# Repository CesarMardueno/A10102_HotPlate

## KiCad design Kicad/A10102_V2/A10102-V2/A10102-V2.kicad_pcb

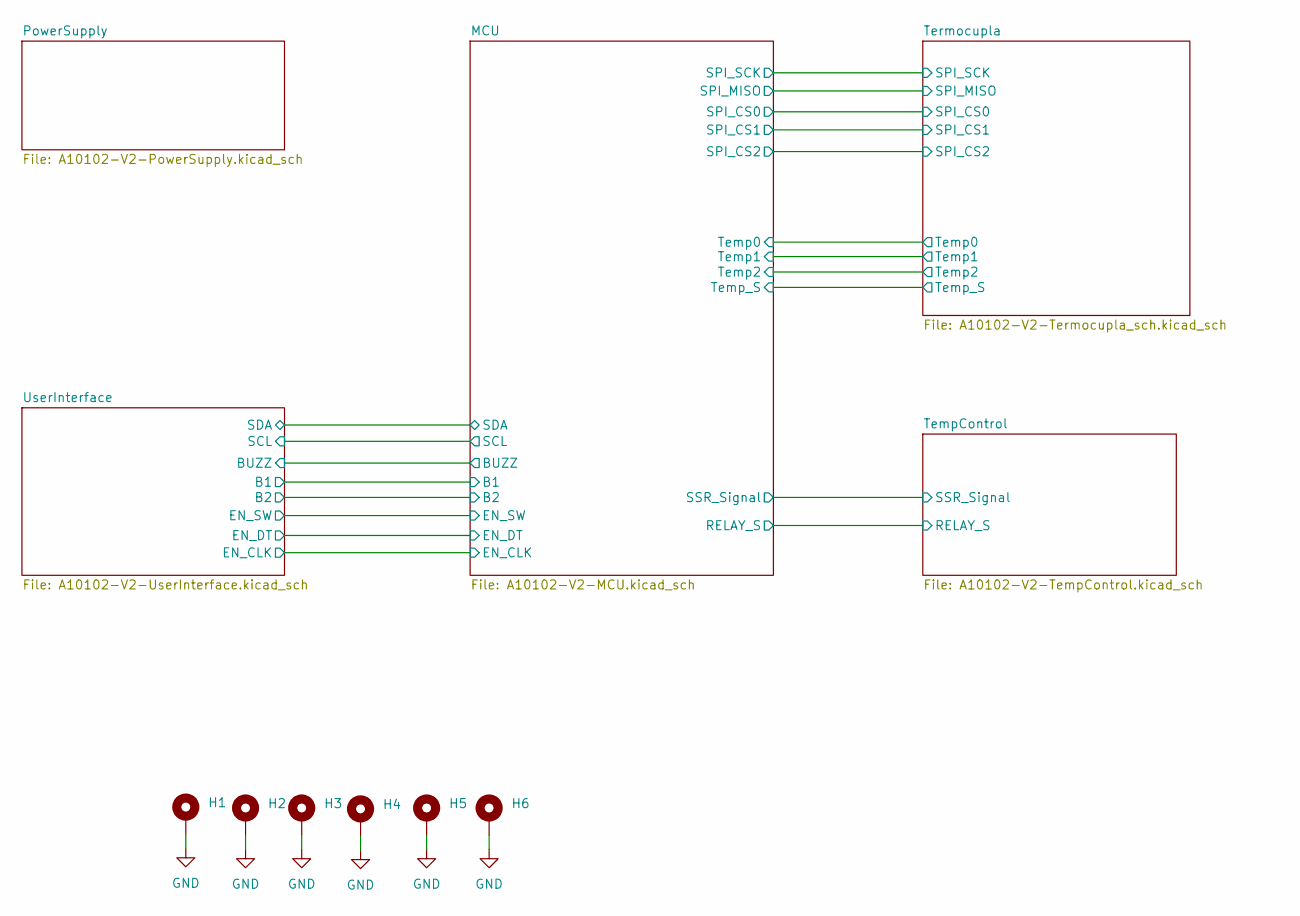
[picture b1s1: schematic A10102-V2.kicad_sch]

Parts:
H1, H2, H3, H4, H5, H6: MountingHole_Pad; MountingHole_3.2mm_M3_ISO7380_Pad

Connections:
GND: H1.1, H2.1, H3.1, H4.1, H5.1, H6.1; also elsewhere on the board

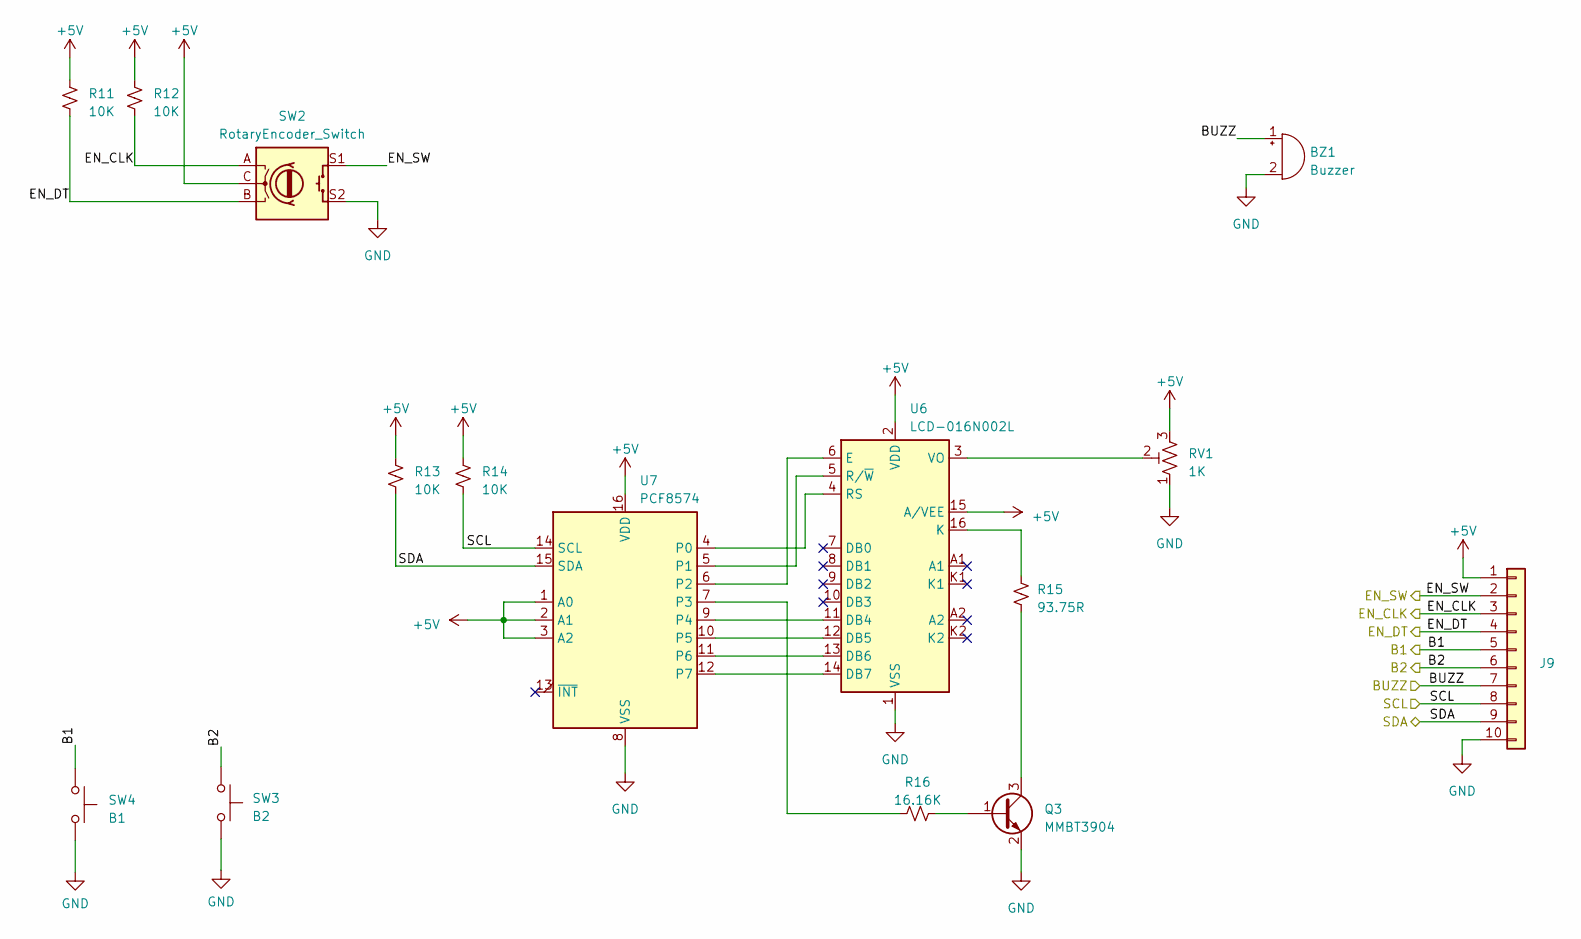
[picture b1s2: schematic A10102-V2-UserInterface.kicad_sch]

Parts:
BZ1: Buzzer; MagneticBuzzer_ProSignal_ABT-410-RC
J9: Conn_01x10; PinHeader_1x10_P2.54mm_Vertical
Q3: MMBT3904; SOT-23
R11, R12, R13, R14: 10K; R_0603_1608Metric_Pad0.98x0.95mm_HandSolder
R15: 93.75R; R_0603_1608Metric_Pad0.98x0.95mm_HandSolder
R16: 16.16K; R_0603_1608Metric_Pad0.98x0.95mm_HandSolder
RV1: 1K; TRIM_3296-W
SW2: RotaryEncoder_Switch; RotaryEncoder_Alps_EC11E-Switch_Vertical_H20mm
SW3: B2; 1TS009C-2400-5000-CT
SW4: B1; 1TS009C-2400-5000-CT
U6: LCD-016N002L
U7: PCF8574; SOIC-16W_7.5x10.3mm_P1.27mm

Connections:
+5V: J9.1, R11.2, R12.2, R13.2, R14.2, RV1.3, SW2.C, U6.2 (VDD), U6.15 (A/VEE), U7.1 (A0), U7.2 (A1), U7.3 (A2), U7.16 (VDD); also elsewhere on the board
/MCU/B1: J9.5, SW4.1; also elsewhere on the board
/MCU/B2: J9.6, SW3.1; also elsewhere on the board
/MCU/BUZZ: BZ1.1 (-), J9.7; also elsewhere on the board
/MCU/EN_CLK: J9.3, R12.1, SW2.A; also elsewhere on the board
/MCU/EN_DT: J9.4, R11.1, SW2.B; also elsewhere on the board
/MCU/EN_SW: J9.2, SW2.S1; also elsewhere on the board
/MCU/SCL: J9.8, R14.1, U7.14 (SCL); also elsewhere on the board
/MCU/SDA: J9.9, R13.1, U7.15 (SDA); also elsewhere on the board
GND: BZ1.2 (+), J9.10, Q3.2 (E), RV1.1, SW2.S2, SW3.2, SW4.2, U6.1 (VSS), U7.8 (VSS); also elsewhere on the board
unnamed: Q3.1 (B), R16.2
unnamed: Q3.3 (C), R15.1
unnamed: U6.11 (DB4), U7.9 (P4)
unnamed: U6.12 (DB5), U7.10 (P5)
unnamed: U6.13 (DB6), U7.11 (P6)
unnamed: U6.14 (DB7), U7.12 (P7)
unnamed: U6.6 (E), U7.6 (P2)
unnamed: R15.2, U6.16 (K)
unnamed: U6.4 (RS), U7.4 (P0)
unnamed: U6.5 (R/~W), U7.5 (P1)
unnamed: RV1.2, U6.3 (VO)
unnamed: R16.1, U7.7 (P3)

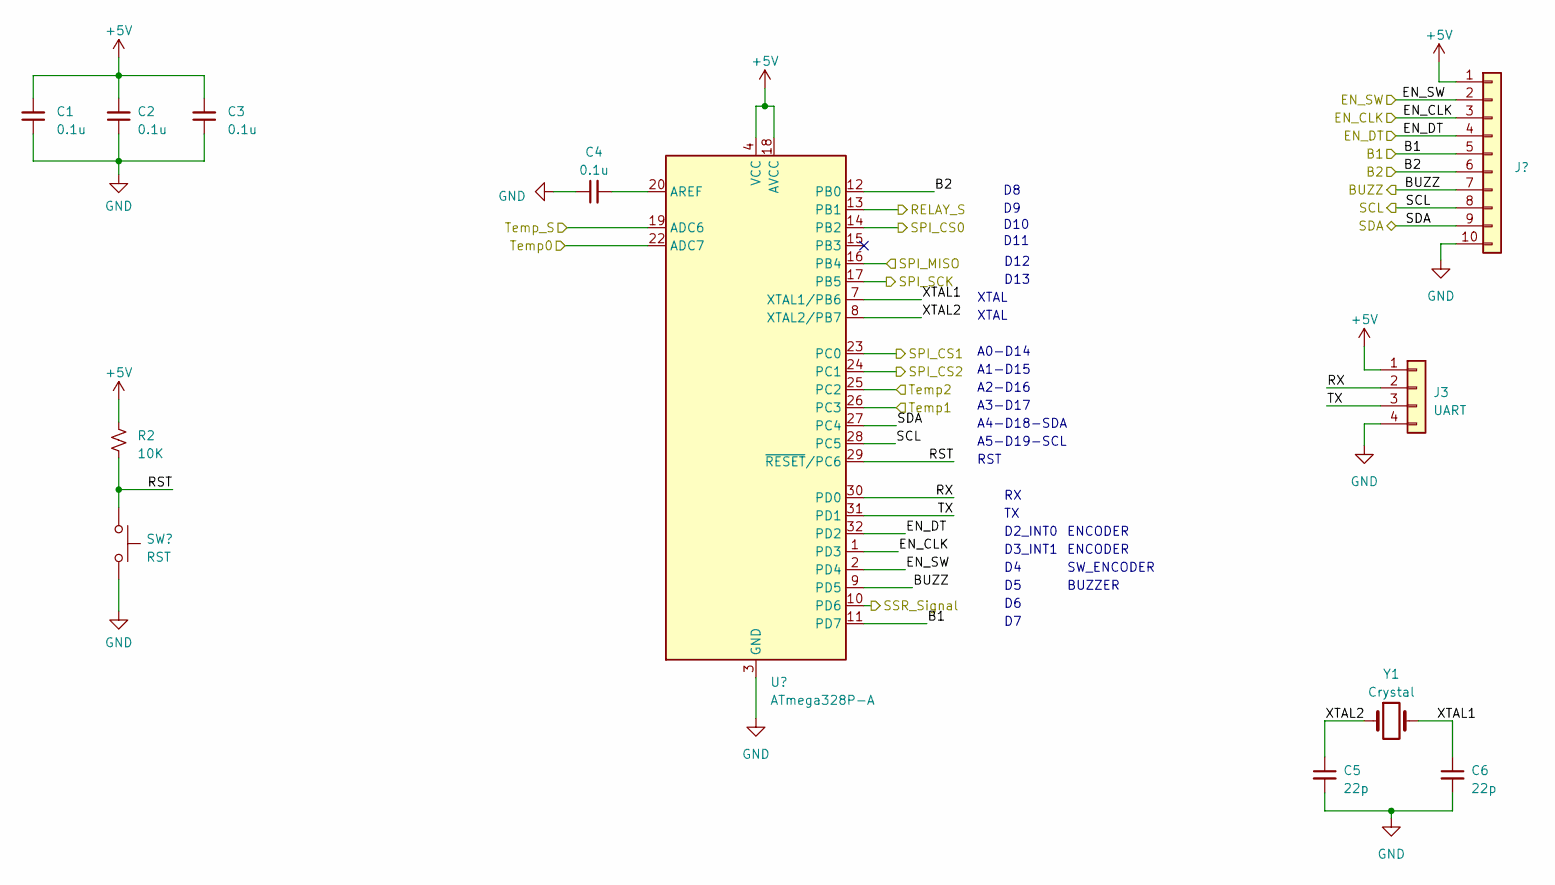
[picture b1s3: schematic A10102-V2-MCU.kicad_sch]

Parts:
C1, C2, C3, C4: 0.1u; C_0603_1608Metric_Pad1.08x0.95mm_HandSolder
C5, C6: 22p; C_0603_1608Metric_Pad1.08x0.95mm_HandSolder
J2: Conn_01x10; PinHeader_1x10_P2.54mm_Vertical
J3: UART; PinHeader_1x04_P2.54mm_Vertical
R2: 10K; R_0603_1608Metric_Pad0.98x0.95mm_HandSolder
SW1: RST; SW_PUSH_6mm_H5mm
U1: ATmega328P-A; TQFP-32_7x7mm_P0.8mm
Y1: Crystal; Crystal_HC52-8mm_Vertical

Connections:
+5V: C1.2, C2.2, C3.2, J2.1, J3.1, R2.1, U1.4 (VCC), U1.6 (VCC), U1.18 (AVCC); also elsewhere on the board
/MCU/B1: J2.5, U1.11 (PD7); also elsewhere on the board
/MCU/B2: J2.6, U1.12 (PB0); also elsewhere on the board
/MCU/BUZZ: J2.7, U1.9 (PD5); also elsewhere on the board
/MCU/EN_CLK: J2.3, U1.1 (PD3); also elsewhere on the board
/MCU/EN_DT: J2.4, U1.32 (PD2); also elsewhere on the board
/MCU/EN_SW: J2.2, U1.2 (PD4); also elsewhere on the board
/MCU/RELAY_S: U1.13 (PB1); also elsewhere on the board
/MCU/RST: R2.2, SW1.1, U1.29 (~RESET/PC6)
/MCU/RX: J3.2, U1.30 (PD0)
/MCU/SCL: J2.8, U1.28 (PC5); also elsewhere on the board
/MCU/SDA: J2.9, U1.27 (PC4); also elsewhere on the board
/MCU/SPI_CS0: U1.14 (PB2); also elsewhere on the board
/MCU/SPI_CS1: U1.23 (PC0); also elsewhere on the board
/MCU/SPI_CS2: U1.24 (PC1); also elsewhere on the board
/MCU/SPI_MISO: U1.16 (PB4); also elsewhere on the board
/MCU/SPI_SCK: U1.17 (PB5); also elsewhere on the board
/MCU/SSR_Signal: U1.10 (PD6); also elsewhere on the board
/MCU/TX: J3.3, U1.31 (PD1)
/MCU/Temp0: U1.22 (ADC7); also elsewhere on the board
/MCU/Temp1: U1.26 (PC3); also elsewhere on the board
/MCU/Temp2: U1.25 (PC2); also elsewhere on the board
/MCU/Temp_S: U1.19 (ADC6); also elsewhere on the board
/MCU/XTAL1: C6.1, U1.7 (XTAL1/PB6), Y1.2
/MCU/XTAL2: C5.1, U1.8 (XTAL2/PB7), Y1.1
GND: C1.1, C2.1, C3.1, C4.1, C5.2, C6.2, J2.10, J3.4, SW1.2, U1.3 (GND), U1.5 (GND), U1.21 (GND); also elsewhere on the board
unnamed: C4.2, U1.20 (AREF)

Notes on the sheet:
SW_ENCODER
A3-D17
A0-D14
BUZZER
A4-D18-SDA
D2_INT0
RST
ENCODER
A1-D15
XTAL
A2-D16
D13
D3_INT1
D10
D11
D12
A5-D19-SCL

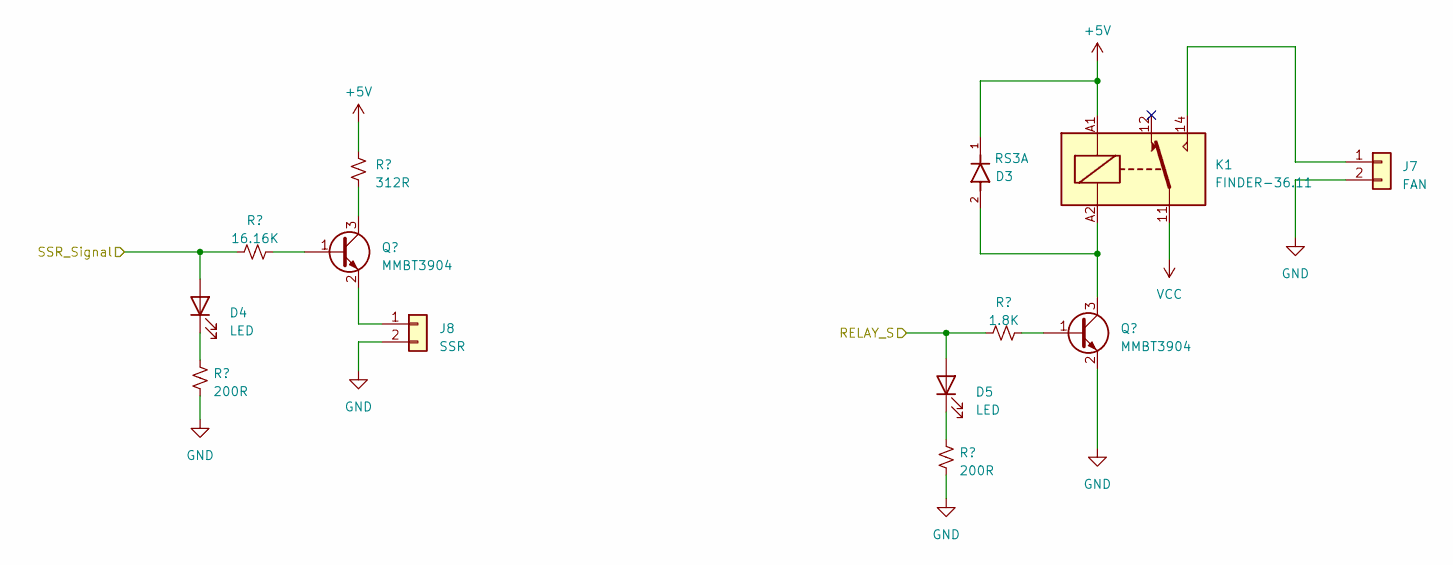
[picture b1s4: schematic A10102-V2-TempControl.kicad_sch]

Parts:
D3: RS3A; D_SMA_Handsoldering; PARTREV L2102
D4, D5: LED; LED_0603_1608Metric_Pad1.05x0.95mm_HandSolder
J7: FAN; JST_XH_B2B-XH-A_1x02_P2.50mm_Vertical
J8: SSR; JST_XH_B2B-XH-A_1x02_P2.50mm_Vertical
K1: FINDER-36.11; Relay_SPDT_Finder_36.11
Q1, Q2: MMBT3904; SOT-23
R6: 312R; R_0603_1608Metric_Pad0.98x0.95mm_HandSolder
R7: 16.16K; R_0603_1608Metric_Pad0.98x0.95mm_HandSolder
R8: 1.8K; R_0603_1608Metric_Pad0.98x0.95mm_HandSolder
R9, R10: 200R; R_0603_1608Metric_Pad0.98x0.95mm_HandSolder

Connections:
+5V: D3.1, K1.A1, R6.2; also elsewhere on the board
/MCU/RELAY_S: D5.2 (A), R8.1; also elsewhere on the board
/MCU/SSR_Signal: D4.2 (A), R7.1; also elsewhere on the board
GND: J7.2, J8.2, Q2.2 (E), R9.1, R10.1; also elsewhere on the board
unnamed: D4.1 (K), R9.2
unnamed: D5.1 (K), R10.2
unnamed: J7.1, K1.14
unnamed: J8.1, Q1.2 (E)
unnamed: Q1.1 (B), R7.2
unnamed: Q1.3 (C), R6.1
unnamed: Q2.1 (B), R8.2
unnamed: D3.2, K1.A2, Q2.3 (C)
VCC: K1.11; also elsewhere on the board

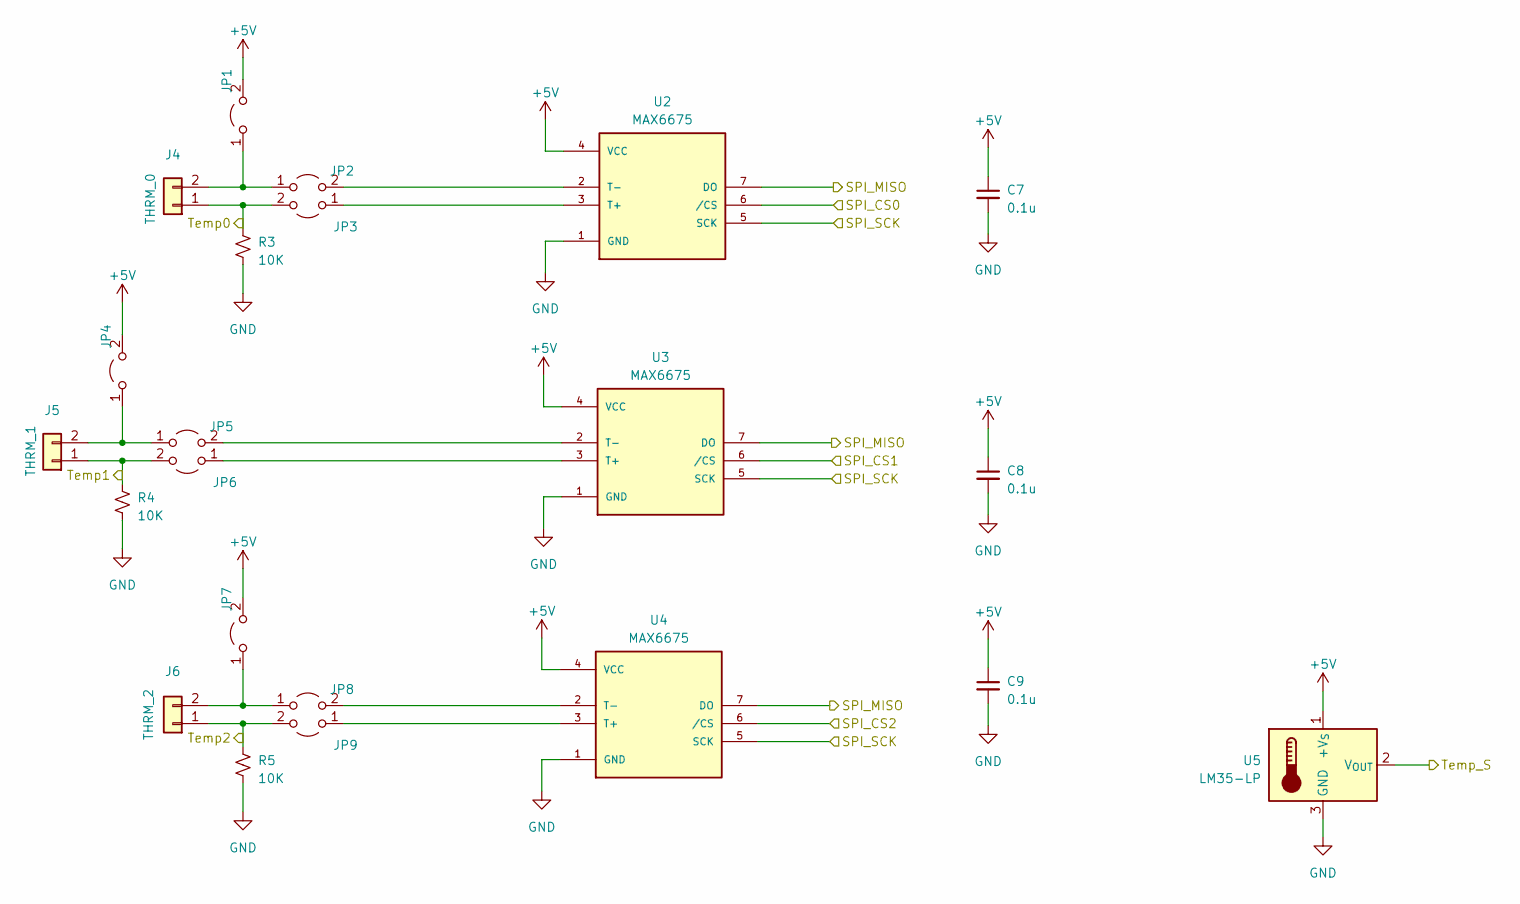
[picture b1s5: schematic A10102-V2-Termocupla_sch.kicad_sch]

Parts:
C7, C8, C9: 0.1u; C_0603_1608Metric_Pad1.08x0.95mm_HandSolder
J4: THRM_0; JST_XH_B2B-XH-A_1x02_P2.50mm_Vertical
J5: THRM_1; JST_XH_B2B-XH-A_1x02_P2.50mm_Vertical
J6: THRM_2; JST_XH_B2B-XH-A_1x02_P2.50mm_Vertical
JP1, JP2, JP3, JP4, JP5, JP6, JP7, JP8, JP9: Jumper_2_Open; SolderJumper-2_P1.3mm_Open_Pad1.0x1.5mm
R3, R4, R5: 10K; R_0603_1608Metric_Pad0.98x0.95mm_HandSolder
U2, U3, U4: MAX6675; SOP-8_3.9x4.9mm_P1.27mm
U5: LM35-LP; TO-92_Inline

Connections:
+5V: C7.1, C8.1, C9.1, JP1.2 (B), JP4.2 (B), JP7.2 (B), U2.4 (VCC), U3.4 (VCC), U4.4 (VCC), U5.1 (+V_{S}); also elsewhere on the board
/MCU/SPI_CS0: U2.6 (/CS); also elsewhere on the board
/MCU/SPI_CS1: U3.6 (/CS); also elsewhere on the board
/MCU/SPI_CS2: U4.6 (/CS); also elsewhere on the board
/MCU/SPI_MISO: U2.7 (DO), U3.7 (DO), U4.7 (DO); also elsewhere on the board
/MCU/SPI_SCK: U2.5 (SCK), U3.5 (SCK), U4.5 (SCK); also elsewhere on the board
/MCU/Temp0: J4.1, JP3.2 (B), R3.1; also elsewhere on the board
/MCU/Temp1: J5.1, JP6.2 (B), R4.1; also elsewhere on the board
/MCU/Temp2: J6.1, JP9.2 (B), R5.1; also elsewhere on the board
/MCU/Temp_S: U5.2 (V_{OUT}); also elsewhere on the board
GND: C7.2, C8.2, C9.2, R3.2, R4.2, R5.2, U2.1 (GND), U3.1 (GND), U4.1 (GND), U5.3 (GND); also elsewhere on the board
unnamed: J4.2, JP1.1 (A), JP2.1 (A)
unnamed: J5.2, JP4.1 (A), JP5.1 (A)
unnamed: J6.2, JP7.1 (A), JP8.1 (A)
unnamed: JP2.2 (B), U2.2 (T-)
unnamed: JP3.1 (A), U2.3 (T+)
unnamed: JP5.2 (B), U3.2 (T-)
unnamed: JP6.1 (A), U3.3 (T+)
unnamed: JP8.2 (B), U4.2 (T-)
unnamed: JP9.1 (A), U4.3 (T+)

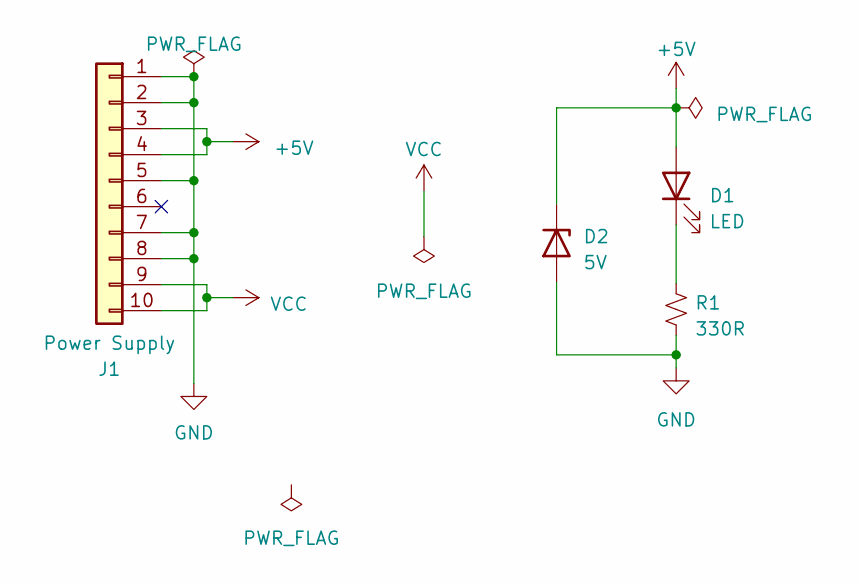
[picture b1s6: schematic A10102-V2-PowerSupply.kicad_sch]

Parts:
D1: LED; LED_0603_1608Metric_Pad1.05x0.95mm_HandSolder
D2: 5V; D_DO-34_SOD68_P7.62mm_Horizontal
J1: Power Supply; PinHeader_1x10_P2.54mm_Vertical
R1: 330R; R_0603_1608Metric_Pad0.98x0.95mm_HandSolder

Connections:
+5V: D1.2 (A), D2.1 (K), J1.3, J1.4; also elsewhere on the board
GND: D2.2 (A), J1.1, J1.2, J1.5, J1.7, J1.8, R1.2; also elsewhere on the board
unnamed: D1.1 (K), R1.1
VCC: J1.9, J1.10; also elsewhere on the board

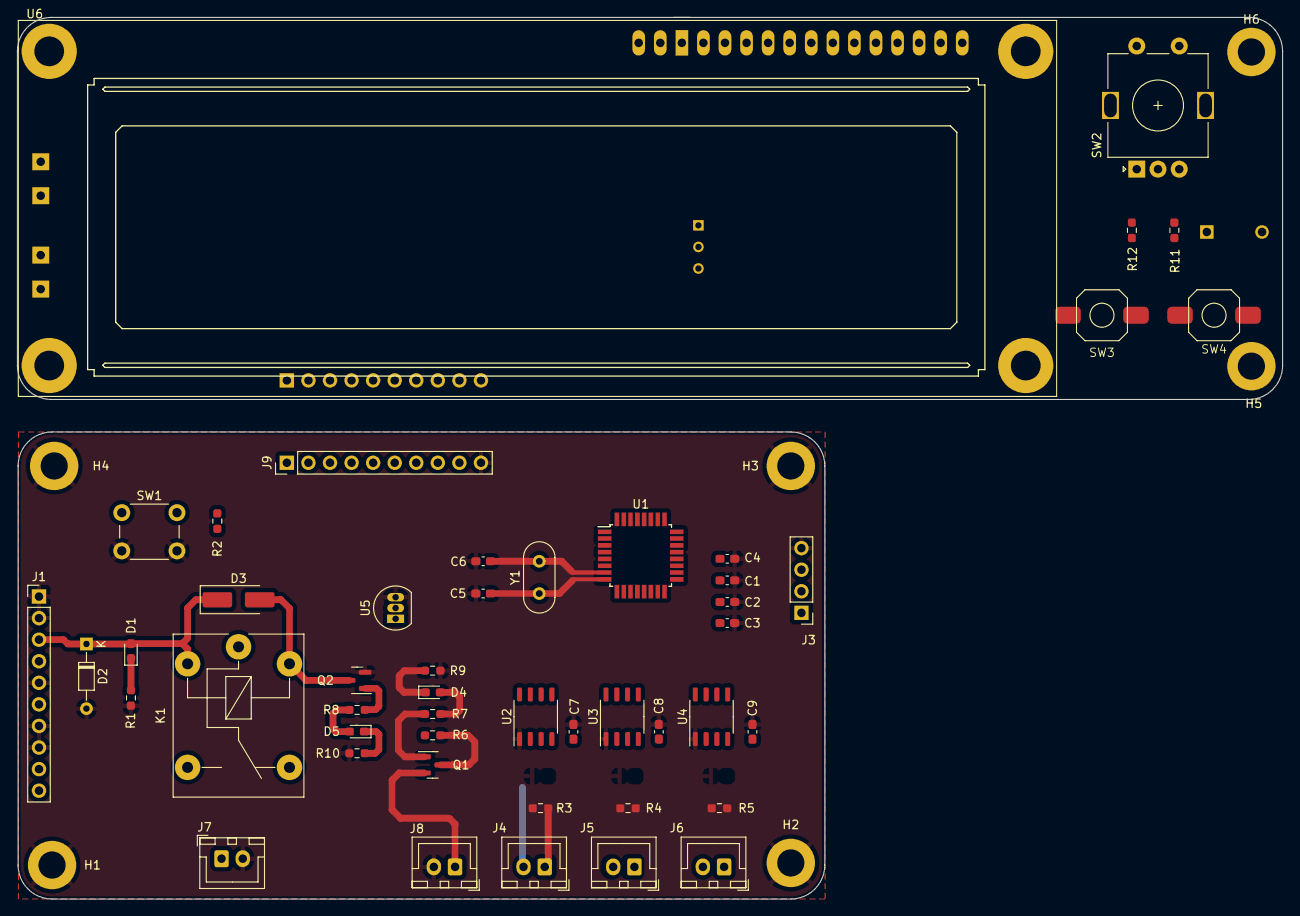
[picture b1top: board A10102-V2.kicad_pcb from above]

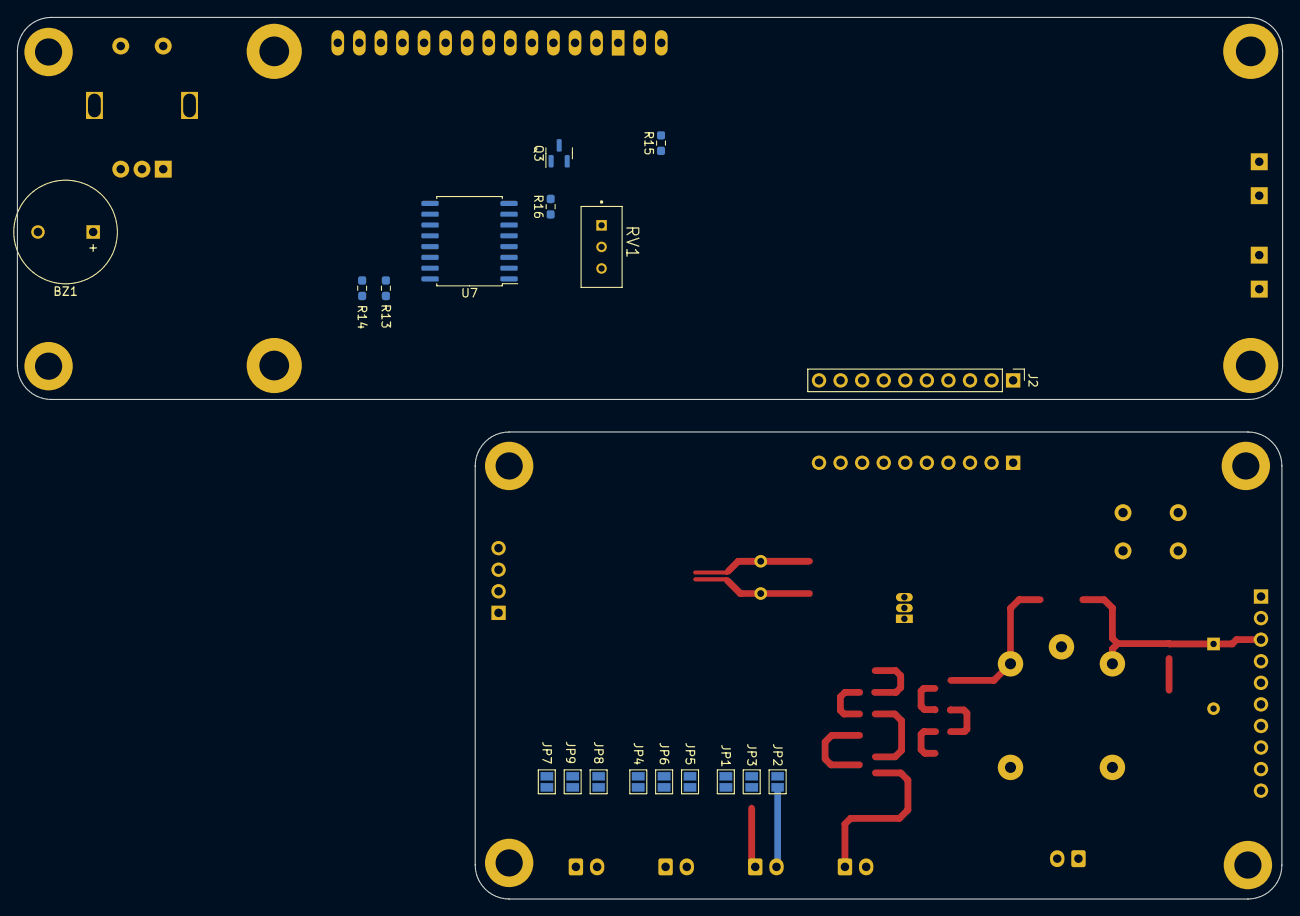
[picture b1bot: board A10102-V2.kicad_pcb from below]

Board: 2 copper layers, 149.0 x 103.8 mm, 72 parts (18 on the bottom side), 58 nets.

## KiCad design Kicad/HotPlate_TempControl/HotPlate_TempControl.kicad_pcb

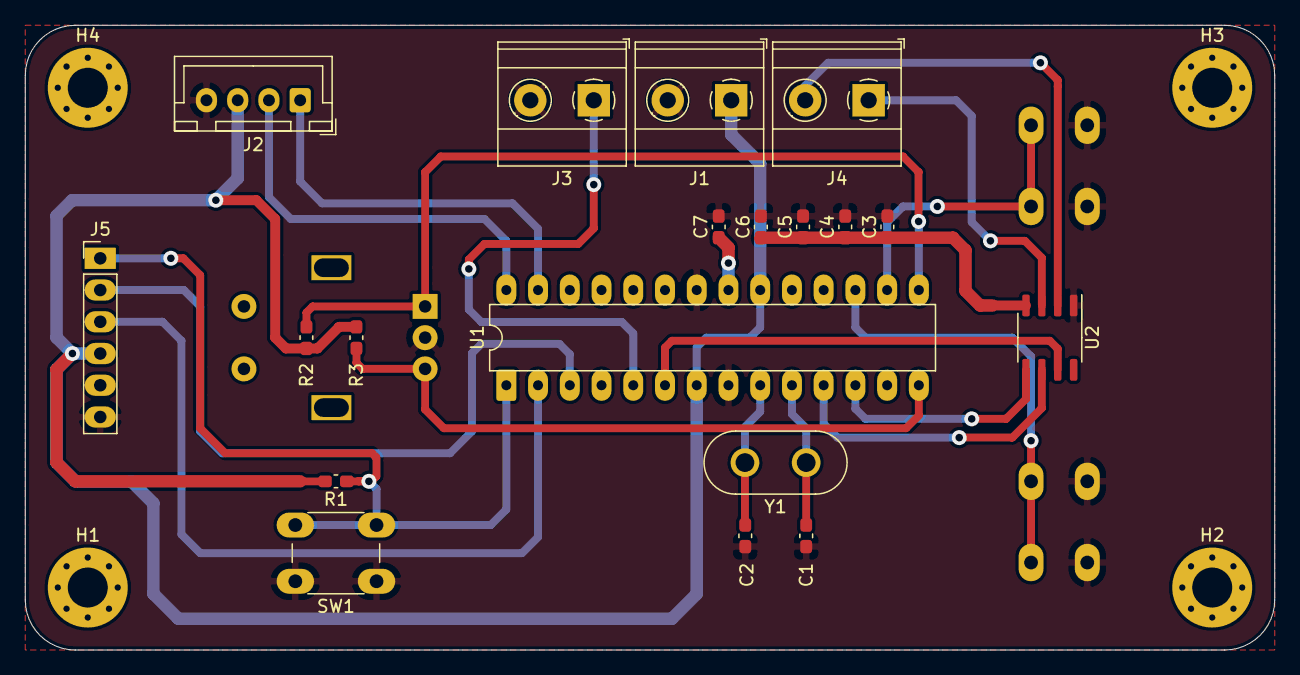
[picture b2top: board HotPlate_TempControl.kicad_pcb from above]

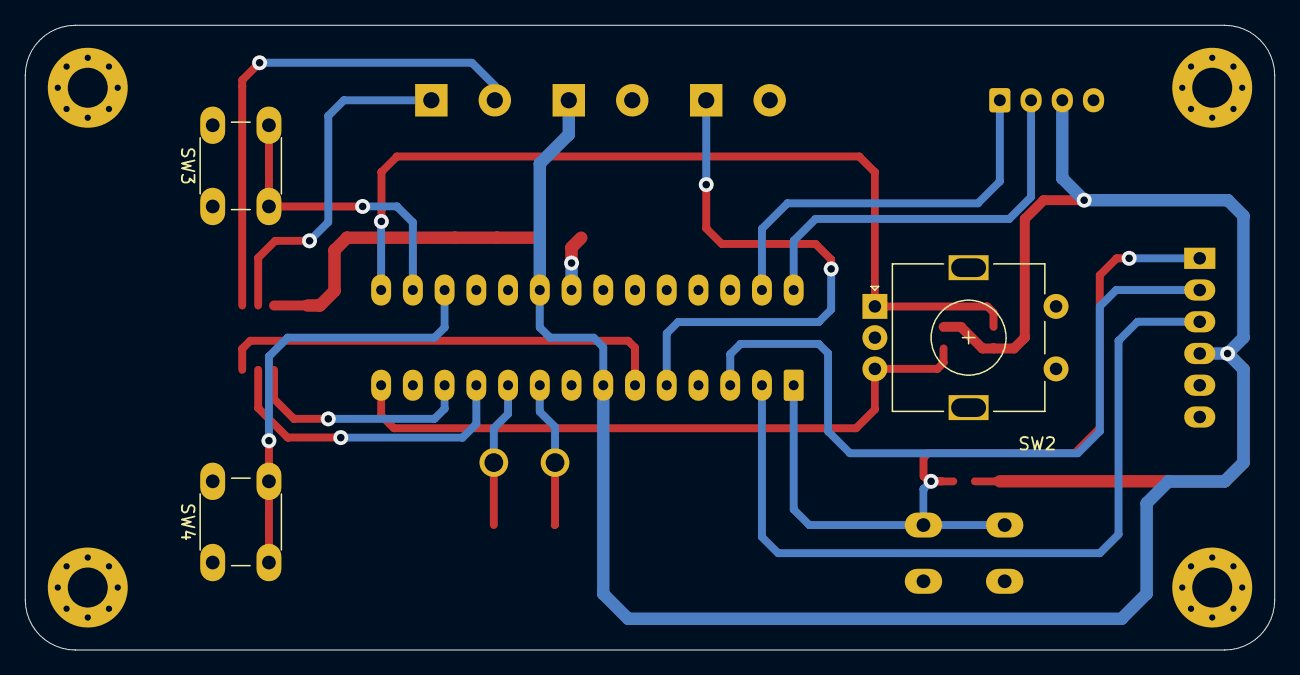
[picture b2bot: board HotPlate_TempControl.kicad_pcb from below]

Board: 2 copper layers, 100.0 x 50.0 mm, 26 parts (3 on the bottom side), 20 nets.

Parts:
C1, C2: 22p; C_0603_1608Metric_Pad1.08x0.95mm_HandSolder
C3, C4, C5, C6, C7: 100n; C_0603_1608Metric_Pad1.08x0.95mm_HandSolder
H1, H2, H3, H4: MountingHole; MountingHole_3.2mm_M3_Pad_Via
J1: POWER; TerminalBlock_Phoenix_MKDS-1,5-2-5.08_1x02_P5.08mm_Horizont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
J2: DISPLAY; JST_XH_B4B-XH-A_1x04_P2.50mm_Vertical
J3: RELAY; TerminalBlock_Phoenix_MKDS-1,5-2-5.08_1x02_P5.08mm_Horizont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
J4: TEMP_SENS; TerminalBlock_Phoenix_MKDS-1,5-2-5.08_1x02_P5.08mm_Horizont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
J5: PROGRAMMER; PinHeader_1x06_P2.54mm_Vertical
R1, R2, R3: 10K; C_0603_1608Metric_Pad1.08x0.95mm_HandSolder
SW1: RESET; SW_PUSH_6mm
SW2: ENCODER; RotaryEncoder_Alps_EC11E-Switch_Vertical_H20mm
SW3, SW4: SW_Push; SW_PUSH_6mm
U1: ATmega328-PU; DIP-28_W7.62mm
U2: MAX6675; SO-8_3.9x4.9mm_P1.27mm
Y1: 16MHZ; Crystal_HC50_Vertical

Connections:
+5V: C3.1, C4.1, C5.1, C6.1, J1.1, J2.3, J5.4, R1.2, R2.2, R3.2, U1.7, U1.20, U2.4
/AREF: C7.1, U1.21
/PB0: R3.1, SW2.B, U1.14
/PB1: R2.1, SW2.A, U1.15
/PB2: SW3.2, U1.16
/PB3: SW4.2, U1.17
/PB6: C2.1, U1.9, Y1.2
/PB7: C1.1, U1.10, Y1.1
/PC4: J2.1, U1.27
/PC5: J2.2, U1.28
/PC6: J5.1, R1.1, SW1.2, U1.1
/PD0: J5.3, U1.2
/PD1: J5.2, U1.3
/PD3: J3.1, U1.5
/PD4: U1.6, U2.7
/PD5: U1.11, U2.6
/PD6: U1.12, U2.5
/T+: J4.1, U2.3
/T-: J4.2, U2.2
GND: C1.2, C2.2, C3.2, C4.2, C5.2, C6.2, C7.2, J1.2, J2.4, J3.2, J5.6, SW1.1, SW2.C, SW3.1, SW4.1, U1.8, U1.22, U2.1

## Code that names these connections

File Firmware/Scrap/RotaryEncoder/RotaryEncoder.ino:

#define en_clk 2
#define en_dt 3
#define en_sw 4

int rotval = 0;   //Contador de pulsos del encoder
bool clkstate = LOW;
bool clklast = HIGH;
bool swstate = HIGH;
bool swlast = HIGH;

void setup() {
  Serial.begin(9600);
  pinMode(en_clk,INPUT);
  pinMode(en_dt,INPUT);
  pinMode(en_sw,INPUT_PULLUP);
}

void loop() {
 readRotary();
 swRotary();

}

void readRotary(){
  clkstate = digitalRead(en_clk);
  if (clkstate != clklast){ //El Encoder se esta moviendo
    Serial.print("Rotary position ");
    if(digitalRead(en_dt) == HIGH){ //Si dt esta en alto mientras se 
      //mueve quiere decir que se mueve negativamente 
      rotval = rotval - 1;
      if(rotval < 0) rotval = 0;
    }
    else{
      rotval++;
      if(rotval > 10) rotval = 10;
    }
    Serial.println(rotval);
    delay(200);
  }
}

void swRotary(){
  swstate = digitalRead(en_sw);
  if(swstate != swlast){
    Serial.println("Rotary pressed");
    delay(100);
  }
  swlast=swstate;
}

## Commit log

2023-07-19 Archivos iniciales
2023-07-19 firmware and block diagram of the project
2023-07-31 TWI Library
2023-08-02 write address
2023-08-13 LCD_Library
2023-12-13 Primera versión de la libreria LCD
2023-12-28 Actualización de archivos
2024-03-21 Se realizaran cambios importantes para refactorizar y poner a prueba el codigo
2024-03-29 Pendiente Validar metodos LCD_PARSER y LCD_SEND
2024-05-09 LCD_16x2 Library finished
2024-05-15 TWI Library funcionaly
2024-06-05 Libreria de lcd por I2c ya escribe caracteres
2024-06-10 Se comienza libreria del max 6675, mas aun no se si funciona SPI
2024-06-14 SPI and MAX6675 functional Library
2024-06-20 Librería enconder funcional
